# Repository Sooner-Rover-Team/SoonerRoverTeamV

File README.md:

---

This is the current code repository for the Sooner Rover Team.

## Active Tasks
[CS Tasks](https://github.com/bentonsmith8/SoonerRoverTeamV/projects/2)

[Electrical Tasks](https://github.com/bentonsmith8/SoonerRoverTeamV/projects/3)

## Previous Repo
[Link to the SoRo-19-20 Repo](https://github.com/eric-plus-plus/SoRo-19-20)

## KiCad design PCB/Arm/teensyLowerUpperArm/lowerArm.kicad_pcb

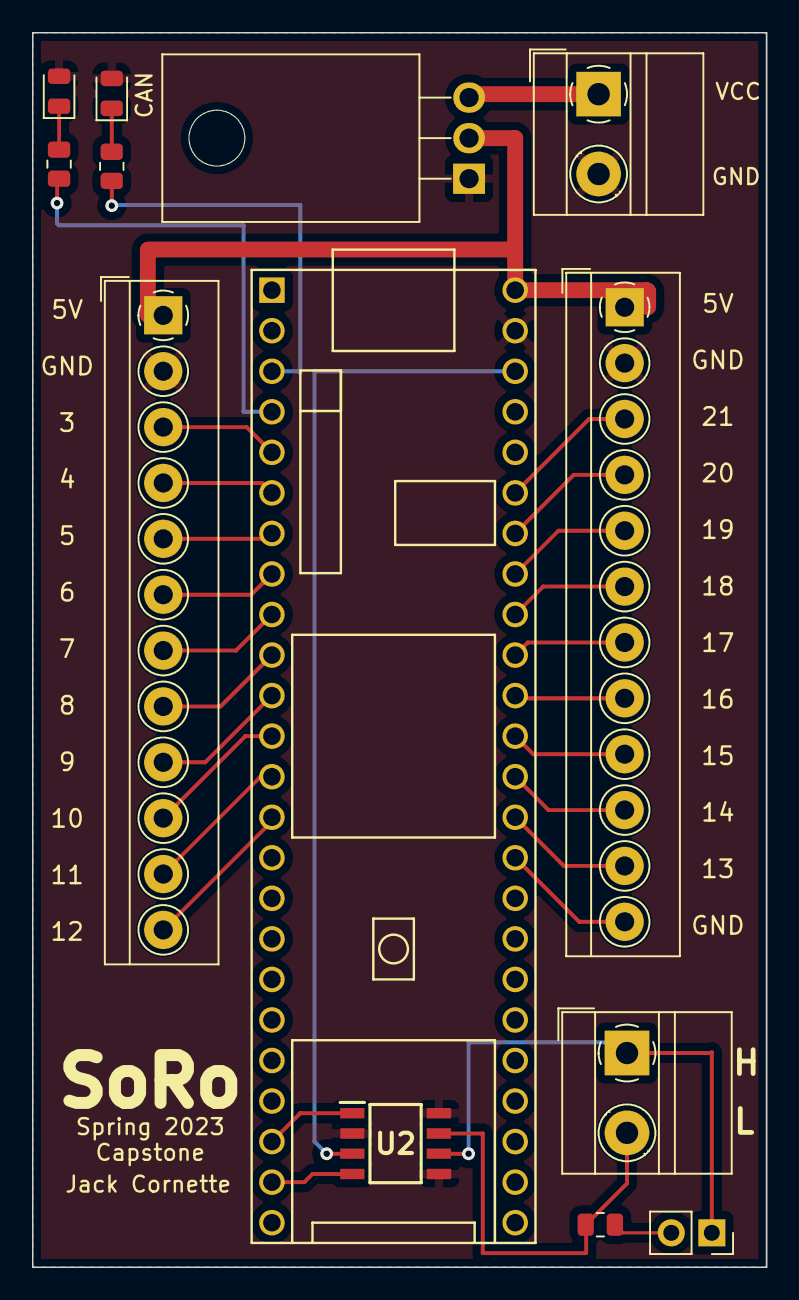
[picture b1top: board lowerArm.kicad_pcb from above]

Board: 2 copper layers, 46.0 x 77.3 mm, 11 parts (0 on the bottom side), 28 nets.

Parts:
CAN: LED_0805_2012Metric
J1, J2: Screw_Terminal_01x12; TerminalBlock_4Ucon_1x12_P3.50mm_Horizontal
J3, J3#2: Screw_Terminal_01x02; TerminalBlock_MetzConnect_Type011_RT05502HBWC_1x02_P5.00mm_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
R3, R3#2, R3#3: R_US; R_0805_2012Metric
U1: LM1084-5.0; TO-220F-3_Horizontal_TabDown
U2: MAX3051; SOIC127P600X175-8N
U3: Teensy4.1; Teensy41_pinHeadOnly

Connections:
3v3: U2.3 (VDD), U3.46 (3V3)
5v: J1.1, J2.1, U1.2 (VO), U3.48 (VIN)
+BATT: J3.1, U1.3 (VI)
GND: CAN.2, J1.2, J2.2, J3.2, U1.1 (GND), U2.2 (GND), U2.5 (SHDN), U2.8 (RS), U3.47 (GND)
unnamed: J1.3, U3.5 (3_LRCLK2)
unnamed: J1.4, U3.6 (4_BCLK2)
unnamed: J1.5, U3.7 (5_IN2)
unnamed: J1.6, U3.8 (6_OUT1D)
unnamed: J1.7, U3.9 (7_RX2_OUT1A)
unnamed: J1.8, U3.10 (8_TX2_IN1)
unnamed: J1.9, U3.11 (9_OUT1C)
unnamed: J1.10, U3.12 (10_CS_MQSR)
unnamed: J1.11, U3.13 (11_MOSI_CTX1)
unnamed: J1.12, U3.14 (12_MISO_MQSL)
unnamed: J2.3, U3.43 (21_A7_RX5_BCLK1)
unnamed: J2.4, U3.42 (20_A6_TX5_LRCLK1)
unnamed: J2.5, U3.41 (19_A5_SCL)
unnamed: J2.6, U3.40 (18_A4_SDA)
unnamed: J2.7, U3.39 (17_A3_TX4_SDA1)
unnamed: J2.8, U3.38 (16_A2_RX4_SCL1)
unnamed: J2.9, U3.37 (15_A1_RX3_SPDIF_IN)
unnamed: J2.10, U3.36 (14_A0_TX3_SPDIF_OUT)
unnamed: J2.11, U3.35 (13_SCK_LED)
unnamed: J2.12, U3.34 (GND)
unnamed: J3#2.2, R3#2.1, U2.7 (CANH)
unnamed: J3#2.1, U2.6 (CANL)
unnamed: U2.1 (TXD), U3.22 (30_CRX3)
unnamed: U2.4 (RXD), U3.23 (31_CTX3)

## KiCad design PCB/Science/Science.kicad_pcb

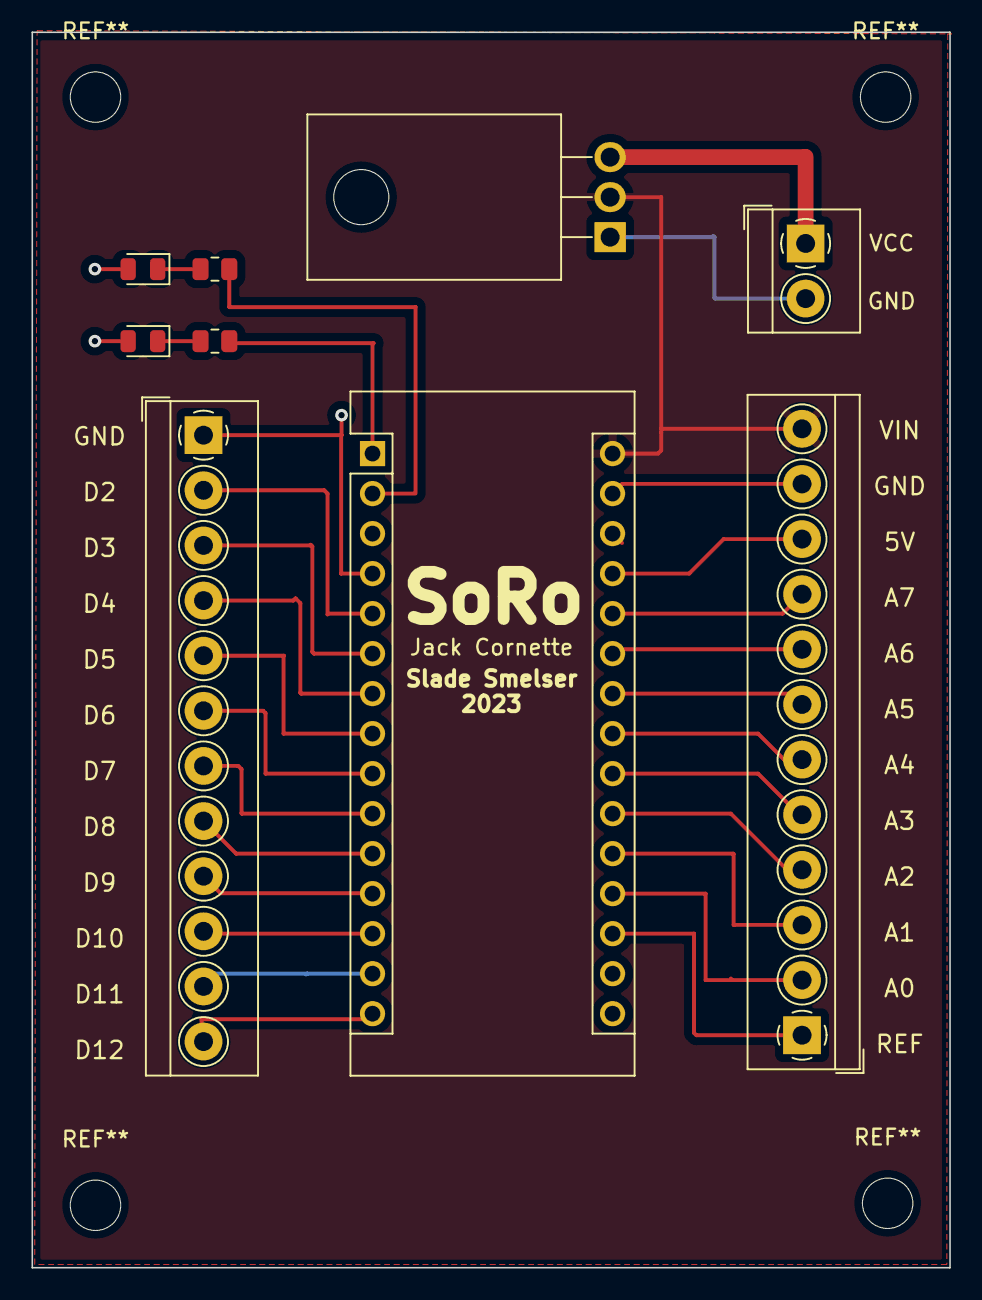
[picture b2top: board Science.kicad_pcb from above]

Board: 2 copper layers, 58.3 x 78.4 mm, 8 parts (0 on the bottom side), 20 nets.

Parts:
A1: Arduino_Nano_v3.x; Arduino_Nano
CAN: LED_0805_2012Metric
J1, J2: Screw_Terminal_01x12; TerminalBlock_4Ucon_1x12_P3.50mm_Horizontal
J3: Screw_Terminal_01x02; TerminalBlock_4Ucon_1x02_P3.50mm_Horizontal
R3, R3#2: R_US; R_0805_2012Metric
U1: LM1084-5.0; TO-220F-3_Horizontal_TabDown

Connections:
+BATT: J3.1, U1.3 (VI)
GND: A1.4 (GND), CAN.2, J1.1, J3.2, U1.1 (GND)
unnamed: A1.6 (D3), J1.3
unnamed: A1.7 (D4), J1.4
unnamed: A1.8 (D5), J1.5
unnamed: A1.9 (D6), J1.6
unnamed: A1.12 (D9), J1.9
unnamed: A1.13 (D10), J1.10
unnamed: A1.15 (D12), J1.12
unnamed: A1.19 (A0), J2.2
unnamed: A1.20 (A1), J2.3
unnamed: A1.21 (A2), J2.4
unnamed: A1.22 (A3), J2.5
unnamed: A1.23 (A4), J2.6
unnamed: A1.24 (A5), J2.7
unnamed: A1.25 (A6), J2.8
unnamed: A1.26 (A7), J2.9
unnamed: A1.27 (+5V), J2.10
unnamed: A1.29 (GND), J2.11
unnamed: A1.30 (VIN), J2.12, U1.2 (VO)

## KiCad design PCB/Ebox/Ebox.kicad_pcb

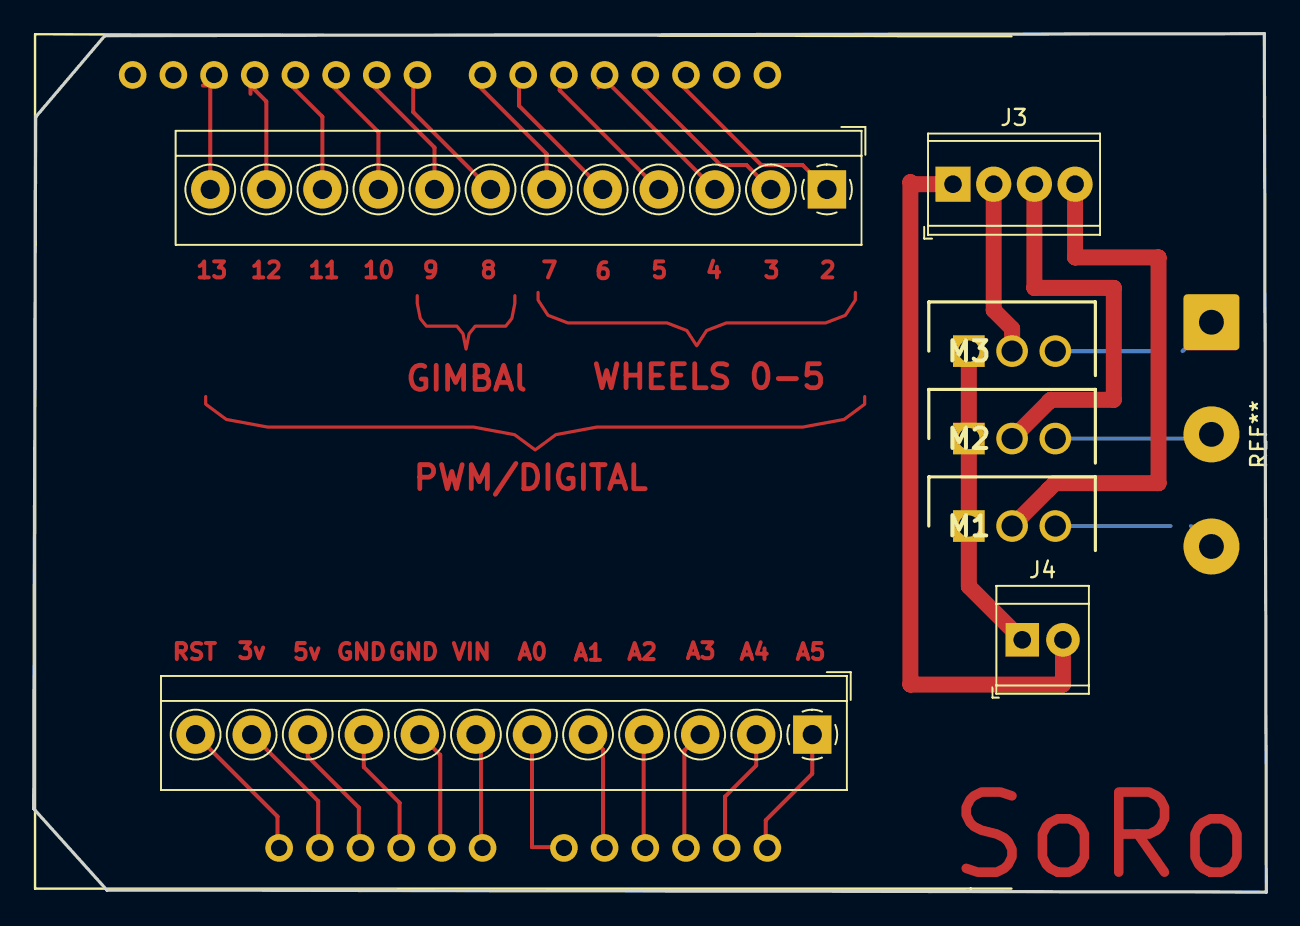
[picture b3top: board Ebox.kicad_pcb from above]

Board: 2 copper layers, 77.0 x 53.6 mm, 8 parts (0 on the bottom side), 29 nets.

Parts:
J1, J2: Screw_Terminal_01x12; TerminalBlock_4Ucon_1x12_P3.50mm_Horizontal
J3: Screw_Terminal_01x04; TerminalBlock_Phoenix_MPT-0,5-4-2.54_1x04_P2.54mm_Horizontal
J4: Screw_Terminal_01x02; TerminalBlock_TE_282834-2_1x02_P2.54mm_Horizontal
M1, M2, M3: MNMOS; TO270P460X1020X2008-3P
XA1: Arduino_Mega2560_Shield

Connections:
unnamed: J1.1, XA1.D2 (D2_INT0)
unnamed: J1.2, XA1.D3 (D3_INT1)
unnamed: J1.3, XA1.D4
unnamed: J1.4, XA1.D5
unnamed: J1.5, XA1.D6
unnamed: J1.6, XA1.D7
unnamed: J1.7, XA1.D8
unnamed: J1.8, XA1.D9
unnamed: J1.9, XA1.D10
unnamed: J1.10, XA1.D11
unnamed: J1.11, XA1.D12
unnamed: J1.12, XA1.D13
unnamed: J2.1, XA1.A5
unnamed: J2.2, XA1.A4
unnamed: J2.3, XA1.A3
unnamed: J2.4, XA1.A2
unnamed: J2.5, XA1.A1
unnamed: J2.6, XA1.A0
unnamed: J2.7, XA1.VIN
unnamed: J2.8, XA1.GND3 (GND)
unnamed: J2.9, XA1.GND2 (GND)
unnamed: J2.10, XA1.5V1 (5V)
unnamed: J2.11, XA1.3V3 (3.3V)
unnamed: J2.12, XA1.RST1 (RESET)
unnamed: J3.1, J4.2
unnamed: J3.2, M3.2 (G)
unnamed: J3.3, M2.2 (G)
unnamed: J3.4, M1.2 (G)
unnamed: J4.1, M1.1 (D), M2.1 (D), M3.1 (D)

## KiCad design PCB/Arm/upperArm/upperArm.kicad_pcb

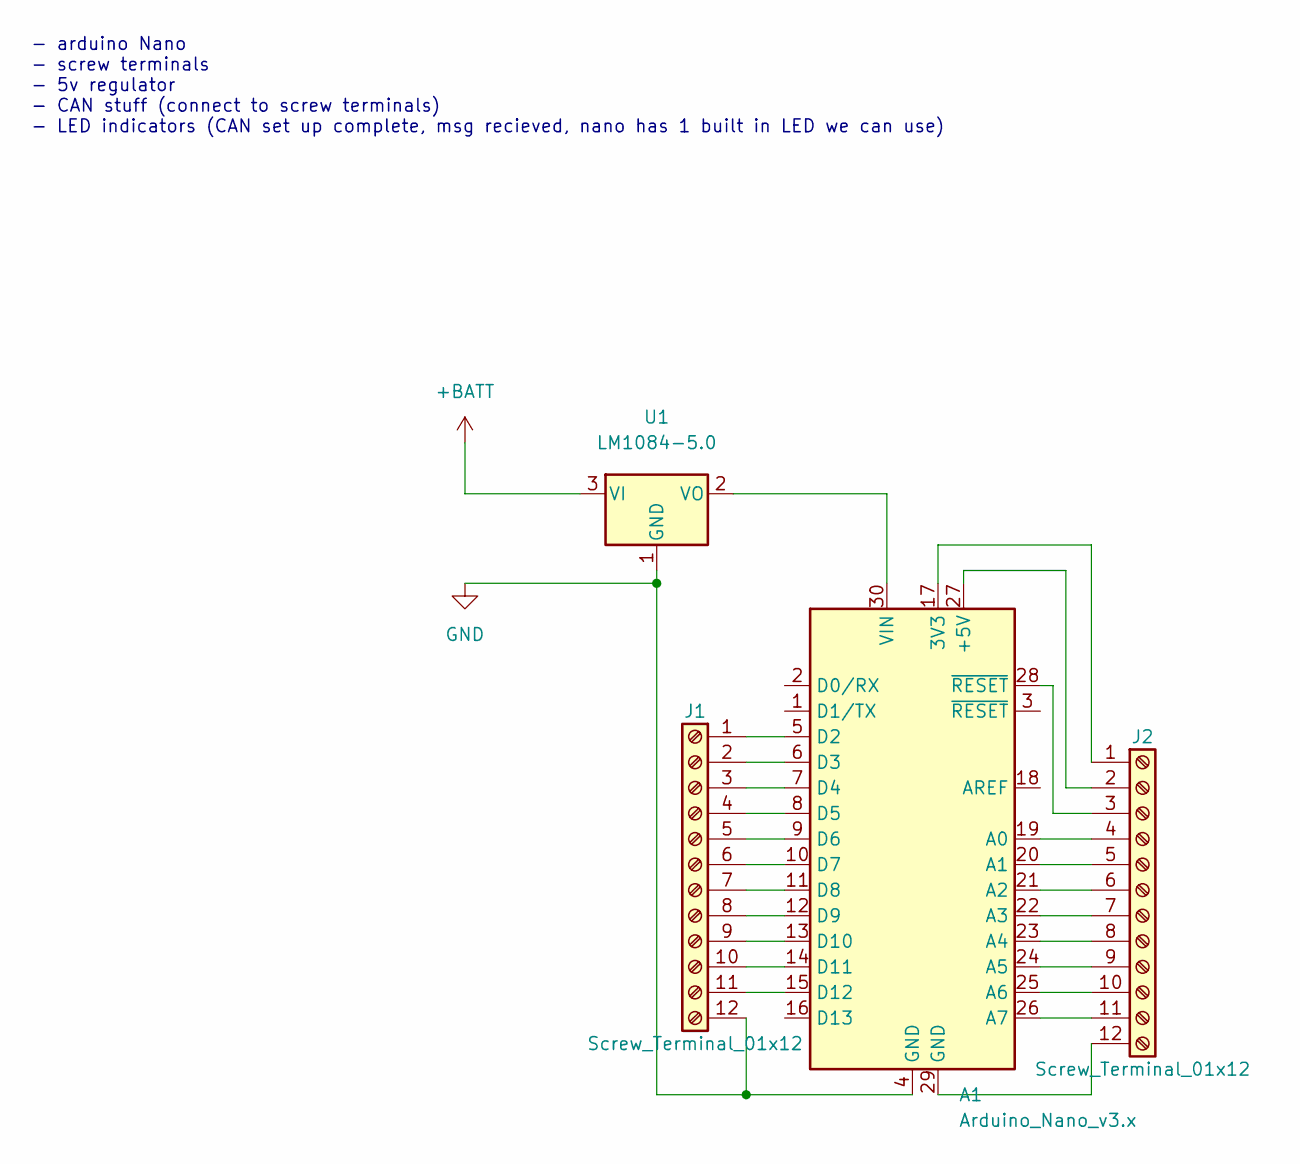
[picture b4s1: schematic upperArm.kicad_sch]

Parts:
A1: Arduino_Nano_v3.x; Arduino_Nano
J1, J2: Screw_Terminal_01x12; TerminalBlock_4Ucon_1x12_P3.50mm_Horizontal
U1: LM1084-5.0; TO-220F-3_Horizontal_TabDown

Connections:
+BATT: U1.3 (VI)
GND: A1.4 (GND), J1.12, U1.1 (GND)
unnamed: A1.5 (D2), J1.1
unnamed: A1.6 (D3), J1.2
unnamed: A1.7 (D4), J1.3
unnamed: A1.8 (D5), J1.4
unnamed: A1.9 (D6), J1.5
unnamed: A1.10 (D7), J1.6
unnamed: A1.11 (D8), J1.7
unnamed: A1.12 (D9), J1.8
unnamed: A1.13 (D10), J1.9
unnamed: A1.14 (D11), J1.10
unnamed: A1.15 (D12), J1.11
unnamed: A1.17 (3V3), J2.1
unnamed: A1.19 (A0), J2.4
unnamed: A1.20 (A1), J2.5
unnamed: A1.21 (A2), J2.6
unnamed: A1.22 (A3), J2.7
unnamed: A1.23 (A4), J2.8
unnamed: A1.24 (A5), J2.9
unnamed: A1.25 (A6), J2.10
unnamed: A1.26 (A7), J2.11
unnamed: A1.27 (+5V), J2.2
unnamed: A1.28 (~RESET), J2.3
unnamed: A1.29 (GND), J2.12
unnamed: A1.30 (VIN), U1.2 (VO)

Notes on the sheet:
- arduino Nano - screw terminals - 5v regulator - CAN stuff (connect to screw terminals) - LED indicators (CAN set up complete, msg recieved, nano has 1 built in LED we can use)

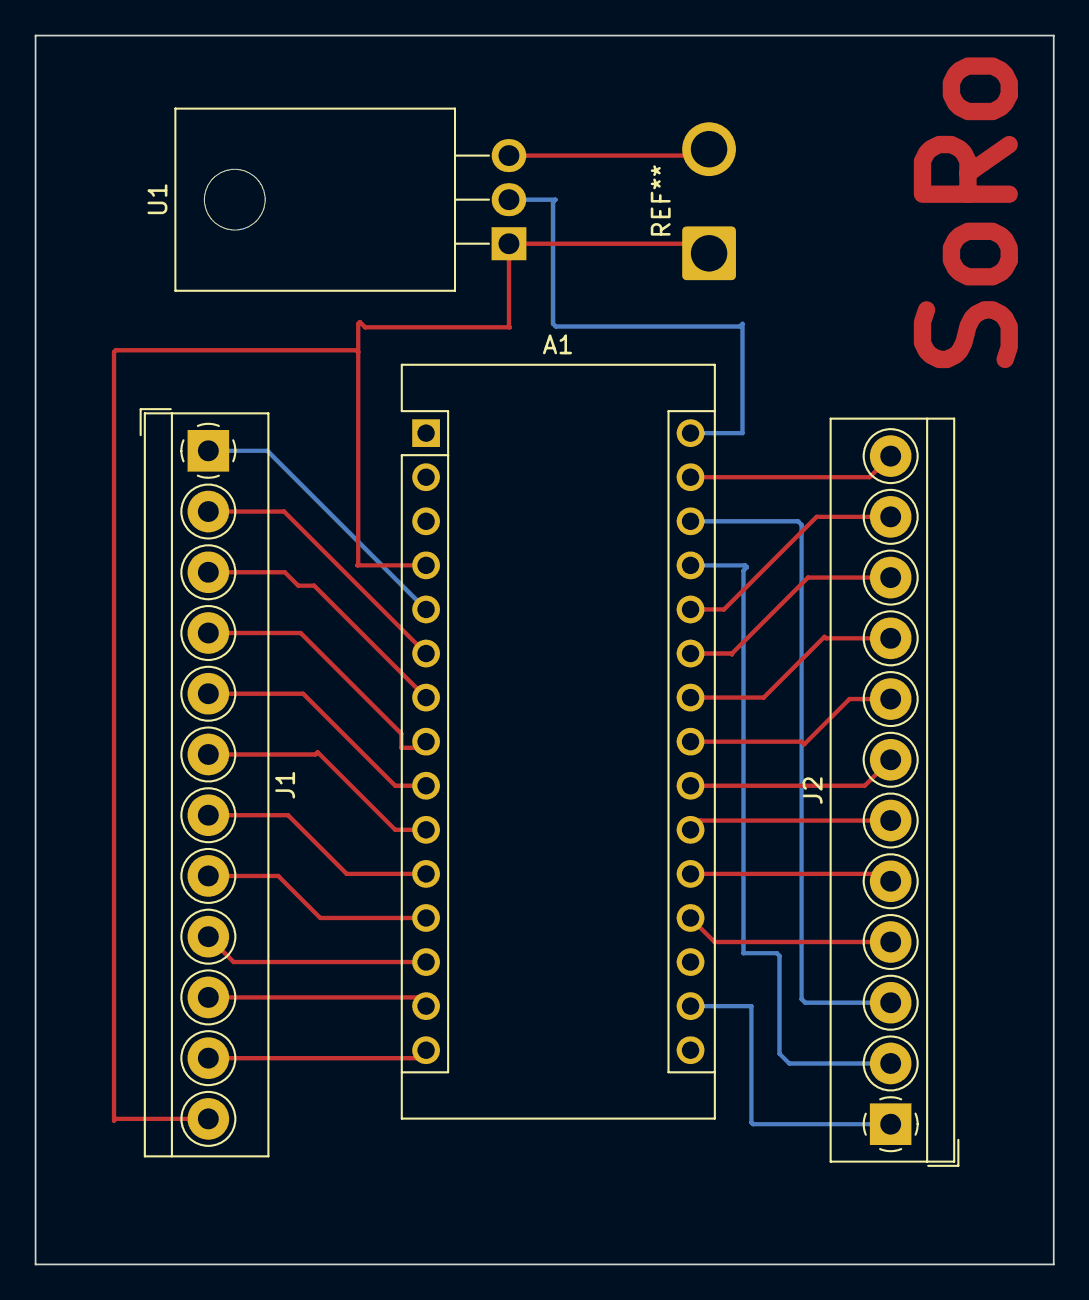
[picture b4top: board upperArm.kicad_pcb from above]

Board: 2 copper layers, 58.7 x 70.8 mm, 4 parts (0 on the bottom side), 25 nets.

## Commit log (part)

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2021-07-23 copied over usable code from previous repo
2021-07-23 set up autonomous folder structure
2021-07-23 added testDayChecklist
2021-09-08 Created working branch to convert ARTracker code to Python.
2021-09-09 Added 2022 rules
2021-09-21 corrected video streamer readme
2021-09-21 Added func definitions
2021-09-23 added typehinting to video streamer code
2021-09-24 added gps libs
2021-09-24 at least it builds and runs, don't know if it works yet
2021-09-24 removed vestigial files
2021-09-24 Revert "Bentongpsstuff"
2021-09-28 added todo list
2021-09-28 updated gitgnore
2021-09-28 Working on using argparse and configparser
2021-10-03 Finished config method
2021-10-15 write sendWheelSpeeds function
2021-10-18 Add files via upload
    _module.so files are able to be imported in python and methods from them should be able to be used.
    import gpsmain
    gpsmain.gpsmain()
    will start the main.c file in python.
2021-10-19 Update main.c
    Change of main() to gpsmain() because main() causes problems with SWIG
2021-10-19 Add files via upload
    Add instructions text
2021-10-19 Update README.md
    Added changes
2021-10-20 Fixed main.c wrapping typo
2021-10-20 Updated SWIG Instructions.txt for Python3
2021-10-20 changed file structure, removed files not related to SWIG wrapping, updated README
2021-10-20 added get position methods to gps.c, gps.h, and gps.i
2021-10-26 Finished constructor and started on arFound
2021-10-26 Updating config sections
2021-10-28 arFound almost done, need to define corners, rejects, MarkerIDs
2021-11-09 wrote most of this stuff
2021-11-09 added getter methods for more things
2021-11-09 fix threading and imports
2021-11-17 finished arFound()
2021-11-29 Create LICENSE
2021-12-18 countValidARs() has been converted
2021-12-19 Finished converting functions to python
2021-12-20 Reorganized some stuff, added an ar example program and fix a ton of ar errors
2021-12-21 Reorganized some stuff
2021-12-21 Started setting up the main drive class
2021-12-22 Cleaned up the print tags
2021-12-22 Created the focal length stuff and reorganized a bit more
2021-12-23 adding the beginner image collector
2021-12-23 added comment
2021-12-24 replacing example code with the correct version :)
2021-12-28 saving images as .txt files
2021-12-29 updated code for user commandline arguments, will need to add AR Tag detection code with Tyler later
2021-12-31 Tyler and Yuki added aruco coordinate stuff to the txt file; we're too cool bruh
2021-12-31 Tyler and Yuki added aruco coordinate stuff to the txt file; we too cool bruh
2022-01-01 Fixed the gate post code in ARTracker and added driveAlongCoordinates to Drive
2022-01-01 Everything is converted except trackARTag
2022-01-02 changed the values of the coordinates
2022-01-02 Added the trackerARMarker method for a single gate post
2022-01-02 Fixed the run script, main.py now takes the cameras as a parameter, fixed small error in drive
2022-01-04 Made the distance measurements with the huddlys take angle into account so they work better now. Still need to add this for gateposts before pulling to master. Someone should also really improve my f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
2022-01-04 Pushing chagnes discussed in zoom
2022-01-07 Debugged gatepost code and improved gate post distance calculations
2022-01-09 Modfied the code to be a bit cleaner and started the process to take in an array of indexes to check for
2022-01-10 tagIDs command prompt user argument
2022-01-10 Fixed the tag sizing
2022-01-10 new command line argument code
2022-01-10 Image collector appears to work now
2022-01-15 Code pretty much works with YOLO now but is far too slow. Should be fixable with GPU and yolo-lite. User must recompile and download the weights before this will run
2022-01-16 Adding .cfg files, the .name file and the image path files
2022-01-18 Made imageCollector a bit better and adding the colab file I used to train everything for postertity. The Colab file still needs to be in google drive to work correctly
2022-01-23 started MBED doc
2022-01-26 uploaded current code
2022-01-26 Added wheel MBED code
2022-01-26 Add files via upload
    Fixed the handling of signed inputs and the range so that it now takes inputs in the range -126 to 126.
2022-01-29 updated MBED code
2022-02-06 started control program
2022-02-07 made function in location.py that takes bearing and distance but returns coordinates, and made comments to clarify functionality.
2022-02-07 updated manual drive
2022-02-08 Saving Reza's testing changes
2022-02-15 wheels move correctly
2022-02-18 Created location method that finds lat and long given bearing and distance
2022-02-19 Modded the checklist a bit and sending proper wheel speeds now
2022-02-19 Fixed bug with i
2022-02-19 Print out the speeds in the setup drive
2022-02-19 Changes at the end of the first test day. Fixed a ton of bugs and chagned speeds to a tuple for some reason
2022-02-19 Cleaned up some of the changes from the test day
2022-02-20 Updated main for easier input, deleted some unneeded files from git
2022-02-20 Cleaned up some code
2022-02-20 Implimented gate post tracking (i know that this is the wrong branch for that but oh well)
2022-02-21 added front and back wheel drive to manual control
2022-02-21 The jetson libraries do not compile on the jetson so I'm not including them. As a result, if you try to use yolo now, it will fail
2022-02-21 fixed config finder for manual drive
2022-02-23 added function in UDPOut to send LED colors
2022-02-23 added an executable for the arm code built for 64 bit windows
2022-02-23 maybe fixed arm code executable
2022-02-25 integrated old arm code into manual_operate (crying emoji)
2022-02-25 fixed more portions of arm code
2022-02-27 updated controller configuration
2022-02-27 removed useless qt arm code
2022-02-27 Added led code and ensured user gives a camera when calling main
2022-02-28 working on getting the carousel moving
2022-02-28 added science package functionality
2022-03-01 added readme to operate
2022-03-01 added config to video streamer
2022-03-02 added drive GUI
2022-03-21 Pushing all the changes I made during the sar preperation. Some of these are not good
2022-04-04 taking all of the changes I made during the sar that I want to keep
2022-04-11 Fixed the error from the SAR
2022-04-11 Create location class to use the z9p GPS instead of the swift
2022-04-11 Add a TODO comment about checking in on the heading and gps coordinate format
2022-04-25 add rovermap
2022-04-26 DO NOT PUSH THESE CHANGES
2022-05-02 tile server
2022-05-02 __file_ needed to be in quotes?
2022-05-02 Aaron fixed the import error
2022-05-16 Fixed many of the autonomous pathing issues and implimented the final programs for the map
2022-05-16 Updated the readme
2022-05-23 changed MBED code
2022-05-24 Setup the max res test
2022-05-28 added new claw control
2022-05-29 Code at the end of May29th test day. Autonomous code is legit working
2022-05-29 leds flash now
2022-05-29 manual operation LEDs comply with URC rules
2022-05-29 Fixed the reconnect issue in autonomous. Benton also did sometihng to client
2022-05-30 added config option to control code
2022-06-01 added rotation and reopening to video streamer
2022-06-03 fixed arm pins and added science gui
2022-06-12 Added a bit of documentation
2022-06-12 Fixed formatting i think
2022-06-12 Fixed formatting i think part 2
2022-06-12 git won't format this right :(. Take 3
2022-06-12 git won't format this right :(. Take 4
2022-06-12 git won't format this right :(. Take 5
2022-06-12 git won't format this right :(. Take 6
2022-10-17 updated rules for 2023
2022-10-20 Added comments markign places with user input, began implementing argparse, replaced latlong code input with argparse input
2022-10-25 Reverted loop to original form, updated latLong to bool, moved argparse to be global, fixed errors
2022-10-25 Removed unused import sys
2022-11-01 Changed latlong option to take a filename and latlong code to read a text file for coordinates
2022-11-01 Added an example text file for latlong coordinate parsing
2022-11-04 Made changes to html template for video streamer
2022-12-12 updated GUI and included folder for background pics
2022-12-22 Added UDP to UDPtoCAN, just needs CAN added to send msgs out
2022-12-22 Added motors to lowerArm, just needs CAN receive implementation
2022-12-22 Wrote basis of upperArm code, still needs CAN and PID implementation
2023-01-02 Created blank PCB files for the Arm
2023-01-02 Created the basis of each PCB, mainly just needs CAN/ LED indicators on each
2023-01-05 Updated Science GUI to match the new package design
2023-01-26 removed .gitignore file from cargo project
2023-02-09 changed makefile for jetson nano
2023-02-15 updated Arm arduino code, manual_operate, and PCBs
2023-02-21 fixed camera arg parsing
2023-02-25 Commented main.py to make it more readable
2023-02-25 Revert "Commented main.py to make it more readable"
    This reverts commit febc574c27e28f07ee3febdb0ac1ee77c6c15828. This
    commit doesn't contribute to readability. For future commits like this,
    it may be wise to conservatively comment instead.
2023-02-25 Changed main.py to take arguments for markers
    Also, I adjusted how all command line arguments are taken from the
    command line. In general, it should be easier to understand how to run
    and use the program without using the README.
    It may be a good idea to start cleaning up other files in this way, but
    for now, this will do :)
2023-02-25 Updated wheel code, organized, added a folder for examples I'vemade
2023-02-26 fixed checksum bug in manual_operate
2023-02-26 added proportional control to wheels
2023-02-28 fixed science package jittering
2023-02-28 added science package test program
2023-03-03 Implemented a method in ARTracker which displays and saves video of the rover tracking the AR tags
2023-03-04 Added function to write and save labeled video of REMI detecting arUco tags; then commented ar.py
2023-03-04 Added more comments to ar.py
2023-04-07 Added new argument to argparser to take id coordinates and default to -1 if none given, removed id parameters from drive, removed commented-out drive functions
2023-04-17 Readded imshow functions
2023-04-20 Finished the Teensy code and new_maual_operate code to function together on rover
2023-04-20 Added some microcontroller examples
2023-04-24 Benton told me to add this; I think he broke the codebase
2023-04-26 Added pictures of Arm to GUI and updated draw_arm_stuff to properly animate the images
2023-04-26 Resolved changes from SAR testing
2023-05-03 proportional control
2023-05-20 Updated speeds on arm motors
2023-05-20 moved lastLoop to top of P loop
2023-05-26 changed stuff
2023-05-31 Added maneuvers folder
2023-05-31 Added backup maneuver which has a file in maneuvers folder and method in Drive.py
2023-06-15 IDK... started a discord bot tho
2023-06-15 Fixed the bot .......
2023-06-15 Added channel ID to config
2023-06-15 chore: Formatted some deps of ARTracker
2023-06-15 fix: Add correct deps for ARTracker
2023-06-16 Restructured bot functions
2023-06-19 Add nasa, quote, and rover functions
2023-06-23 Changes to Auto made at SAR (Pls don't break)
2023-07-10 Improved Discord bot Calendar feature
2023-09-20 config
2023-09-21 fix: Adjust more paths in new_manual_operate.py
    (replaces broken NTFS paths)
2023-09-29 Reorganized code
2023-09-29 Wireless controller code
2023-09-29 No need for separate scripts
2023-10-19 python socket stuff
2023-10-25 Encoder stuff
2023-10-25 Fixes
2023-11-01 upper
2023-11-02 UpperArm
2023-11-09 Fixed wireless comm issues
2023-11-09 cleaned up some stuff
2023-11-30 Working now?
2023-11-30 Revert "Working now?"
    This reverts commit 9a4533e6c2ff0a848396f802731e31ac875d283a.
2023-11-30 Working now
2023-11-30 Revert "Working now"
    This reverts commit a889cddc244cb8ab895beded37787aef463ee64d.
2024-02-02 Old stuff and wifi
